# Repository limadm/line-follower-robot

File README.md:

View this project on [CADLAB.io](https://cadlab.io/node/934). 

# Simple line follower robot

---

A small robot in one board, for educational purposes.

---

Copyright © 2014 Daniel Lima

Software under MIT License, other assets under Creative Commons CC-BY 4.0.

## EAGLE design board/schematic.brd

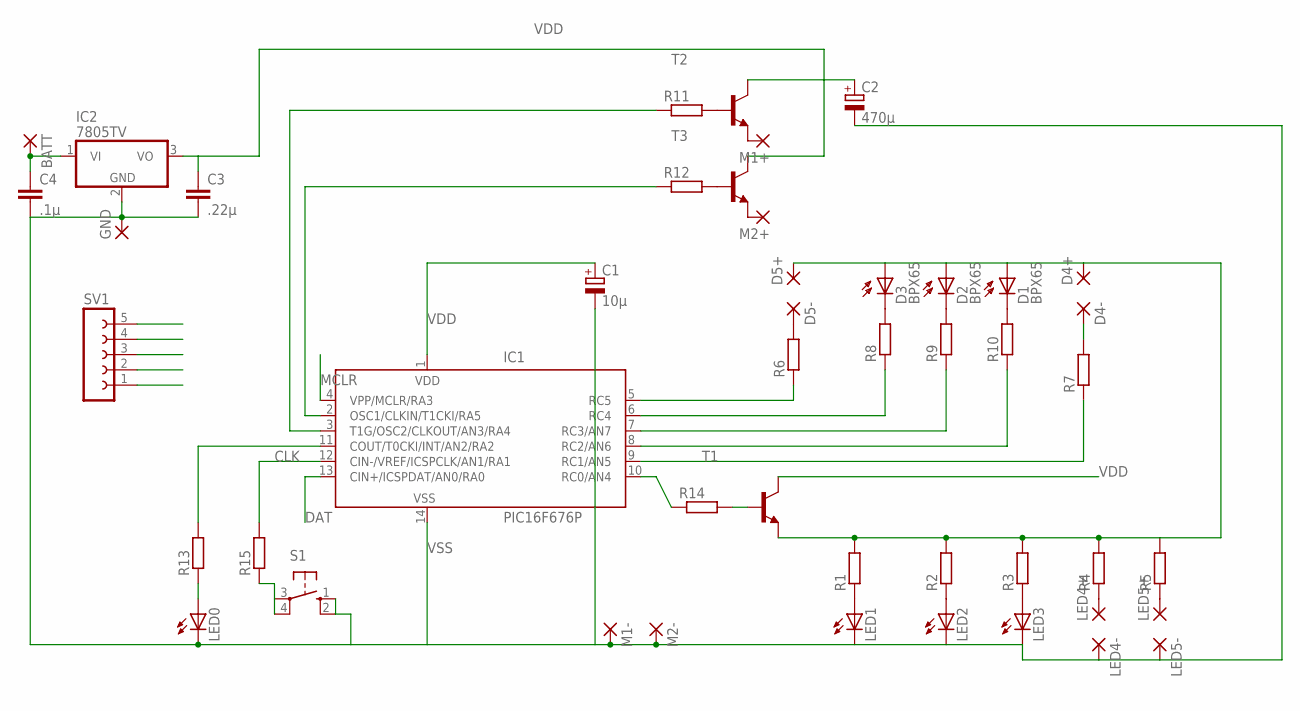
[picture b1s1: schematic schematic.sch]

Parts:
BATT: 2,15/1,0
C1: 10µ; E2,5-5
C2: 470µ; E2,5-7
C3: .22µ; C050-025X075
C4: .1µ; C050-025X075
D1, D2, D3: BPX65
D4+, D4-, D5+, D5-: 2,15/1,0
GND: 2,15/1,0
IC1: PIC16F676P; DIL14
IC2: 7805TV; TO220V
LED0, LED1, LED2, LED3: LED3MM
LED4+, LED4-, LED5+, LED5-: 2,15/1,0
M1+, M1-, M2+, M2-: 2,15/1,0
R1, R2, R3, R4, R5, R6, R7, R8, R9, R10, R11, R12, R13, R14, R15: R-EU_0204/7; 0204/7
S1: 10-XX; B3F-10XX
SV1: FE05-1
T1, T2, T3: -NPN-TO92; TO92

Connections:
CLK: IC1.12 (CIN-/VREF/ICSPCLK/AN1/RA1), R15.2, SV1.5
DAT: IC1.13 (CIN+/ICSPDAT/AN0/RA0), SV1.4
MCLR: IC1.4 (VPP/MCLR/RA3), SV1.1
unnamed: D1.A, D2.A, D3.A, D4+.1, D5+.1, R1.2, R2.2, R3.2, R4.2, R5.2, T1.1 (E)
unnamed: LED1.A, R1.1
unnamed: LED2.A, R2.1
unnamed: LED3.A, R3.1
unnamed: LED4+.1, R4.1
unnamed: LED5+.1, R5.1
unnamed: LED0.A, R13.1
unnamed: IC1.10 (RC0/AN4), R14.1
unnamed: R14.2, T1.2 (B)
unnamed: IC1.6 (RC4), R8.1
unnamed: D5-.1, R6.2
unnamed: D4-.1, R7.2
unnamed: D3.K (C), R8.2
unnamed: D2.K (C), R9.2
unnamed: D1.K (C), R10.2
unnamed: IC1.5 (RC5), R6.1
unnamed: IC1.7 (RC3/AN7), R9.1
unnamed: IC1.8 (RC2/AN6), R10.1
unnamed: IC1.9 (RC1/AN5), R7.1
unnamed: BATT.1, C4.1, IC2.1 (VI)
unnamed: IC1.11 (COUT/T0CKI/INT/AN2/RA2), R13.2
unnamed: M1+.1, T2.1 (E)
unnamed: M2+.1, T3.1 (E)
unnamed: R12.2, T3.2 (B)
unnamed: R11.2, T2.2 (B)
unnamed: IC1.2 (OSC1/CLKIN/T1CKI/RA5), R12.1
unnamed: IC1.3 (T1G/OSC2/CLKOUT/AN3/RA4), R11.1
unnamed: R15.1, S1.3, S1.4 (P1)
VDD: C1.+, C2.+, C3.1, IC1.1 (VDD), IC2.3 (VO), SV1.2, T1.3 (C), T2.3 (C), T3.3 (C)
VSS: C1.-, C2.-, C3.2, C4.2, GND.1, IC1.14 (VSS), IC2.2 (GND), LED0.K (C), LED1.K (C), LED2.K (C), LED3.K (C), LED4-.1, LED5-.1, M1-.1, M2-.1, S1.1 (S), S1.2 (S1), SV1.3

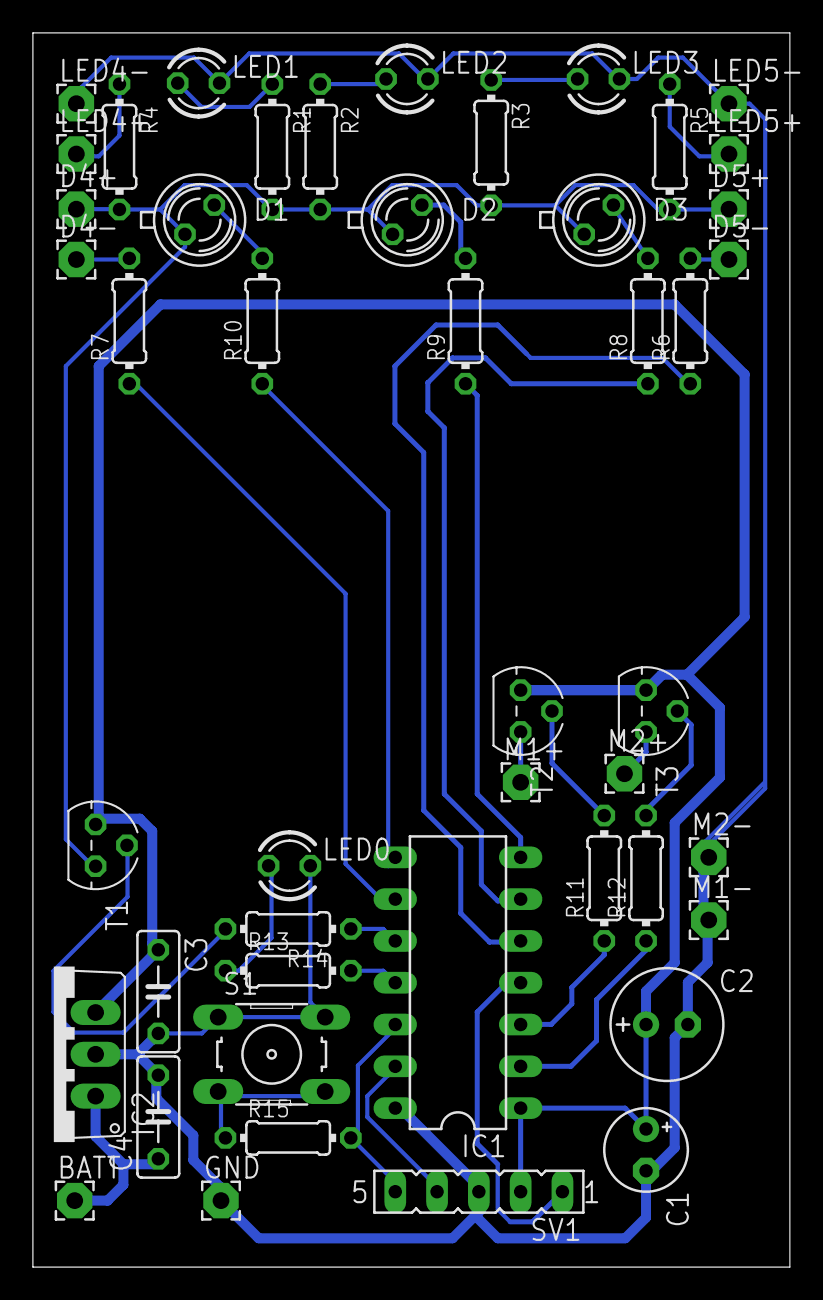
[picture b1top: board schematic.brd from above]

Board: 2 copper layers, 46.0 x 75.0 mm, 47 parts (0 on the bottom side), 33 nets.

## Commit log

2015-09-26 README.md edited online with Bitbucket
2018-04-25 Backlink to CADLAB.io has been added.
